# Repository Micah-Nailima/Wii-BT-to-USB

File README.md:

# Wii BT to USB
 A conversion for Wii bluetooth adapters to be used via USB on PC's
 PCB's for both the WML-C43 and J27H002 bluetooth adapters found within the Nintendo Wii

WML-C43 is a Kicad Project
Wii Bluetooth Module is an Eagle project (i know, someone's gonna get mad cause I use both)

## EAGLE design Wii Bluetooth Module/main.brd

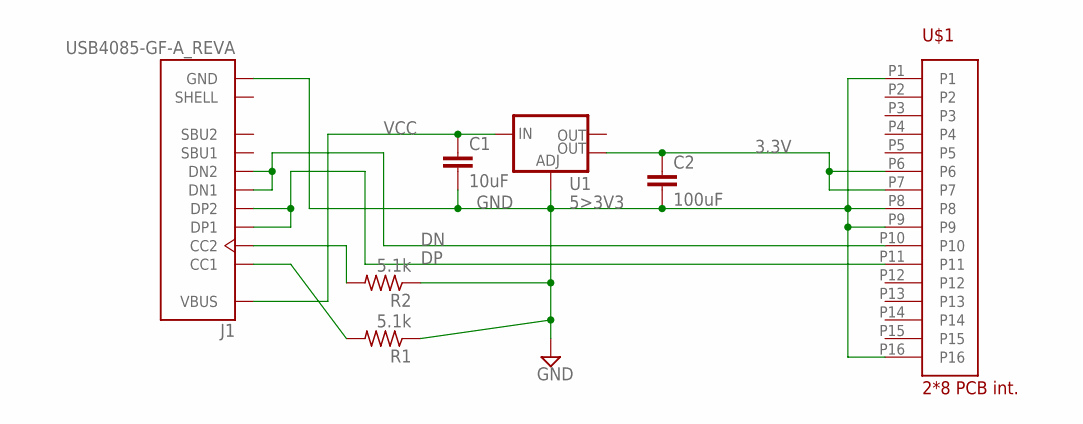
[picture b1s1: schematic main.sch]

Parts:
C1: 10uF; C0805
C2: 100uF; C0805
J1: USB4085-GF-A_REVA; GCT_USB4085-GF-A_REVA
R1, R2: 5.1k; R0805
U1: 5>3V3; SOT223
U$1: MOLEX_0541020164MOLEX; MOLEX_0541020164

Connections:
3.3V: C2.1, U1.4 (OUT), U$1.P6, U$1.P7
DN: J1.A7 (DN1), J1.B7 (DN2), U$1.P10
DP: J1.A6 (DP1), J1.B6 (DP2), U$1.P11
GND: C1.2, C2.2, J1.A1 (GND), J1.A12 (GND), J1.B1 (GND), J1.B12 (GND), R1.1, R2.1, U1.1 (ADJ), U$1.P1, U$1.P8, U$1.P9, U$1.P16
unnamed: J1.B5 (CC2), R2.2
unnamed: J1.A5 (CC1), R1.2
VCC: C1.1, J1.A4 (VBUS), J1.A9 (VBUS), J1.B4 (VBUS), J1.B9 (VBUS), U1.3 (IN)

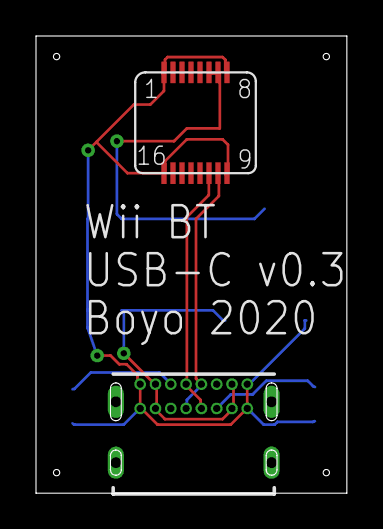
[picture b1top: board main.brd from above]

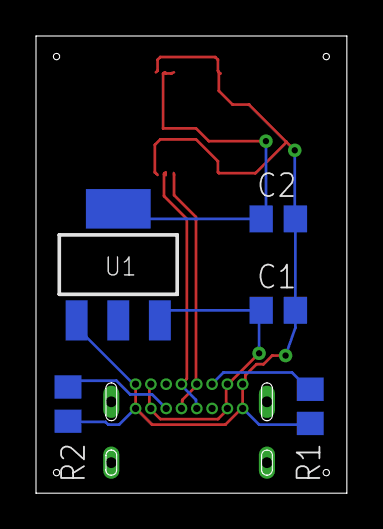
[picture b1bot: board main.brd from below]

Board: 2 copper layers, 17.3 x 25.4 mm, 7 parts (5 on the bottom side), 7 nets.

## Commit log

2020-08-06 Added AcheronLibrary
2020-08-06 WML-C43
    added libraries
    added project files
2020-08-07 power supply and esd protection
2020-09-03 50% done
    +footprint and symbol for WML-C43 Molex Connector
    +pcb
    +schematic finished
2020-09-27 uploaded original eagle project
2020-10-07 eagle project updated
2020-11-12 pcb finish i think
2021-03-12 v0.4
    -added USB data pin ESD protection
    -added low pass filter to deal with noise on VCC/+5v
    -fixed the slim stack connector pinout cause the 1-8 row was flipped because my brain is pepega
2021-03-12 removed gerbers
2021-03-12 Update fp-info-cache

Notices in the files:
parts and their libraries:
SparkFun-IC-Power: Licensing: Creative Commons ShareAlike 4.0 International - https://creativecommons.org/licenses/by-sa/4.0
